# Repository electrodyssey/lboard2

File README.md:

experimental sound processing board with XC6SLX9-TQG144 and TLV320AIC3204

Work is in progress. 

Currently board is capable of receiving and sending the audio samples with a codec and passes the loopback test from FPGA pins.

FPGA bitstream config is stored inside the STM32F401RE internal flash.

Quick and dirty firmware loader is here: https://github.com/electrodyssey/lboard2flashboot

Working full-duplex aic3204 configuration script is saved in aic3204script directory:

codec receives: MCLK = 11.2896 MHz,

and generates: BLCK = 2.8224 MHz,

WCLK = 44.1 kHz

Please check the CHANGELOG  for the updates

Block diagram:

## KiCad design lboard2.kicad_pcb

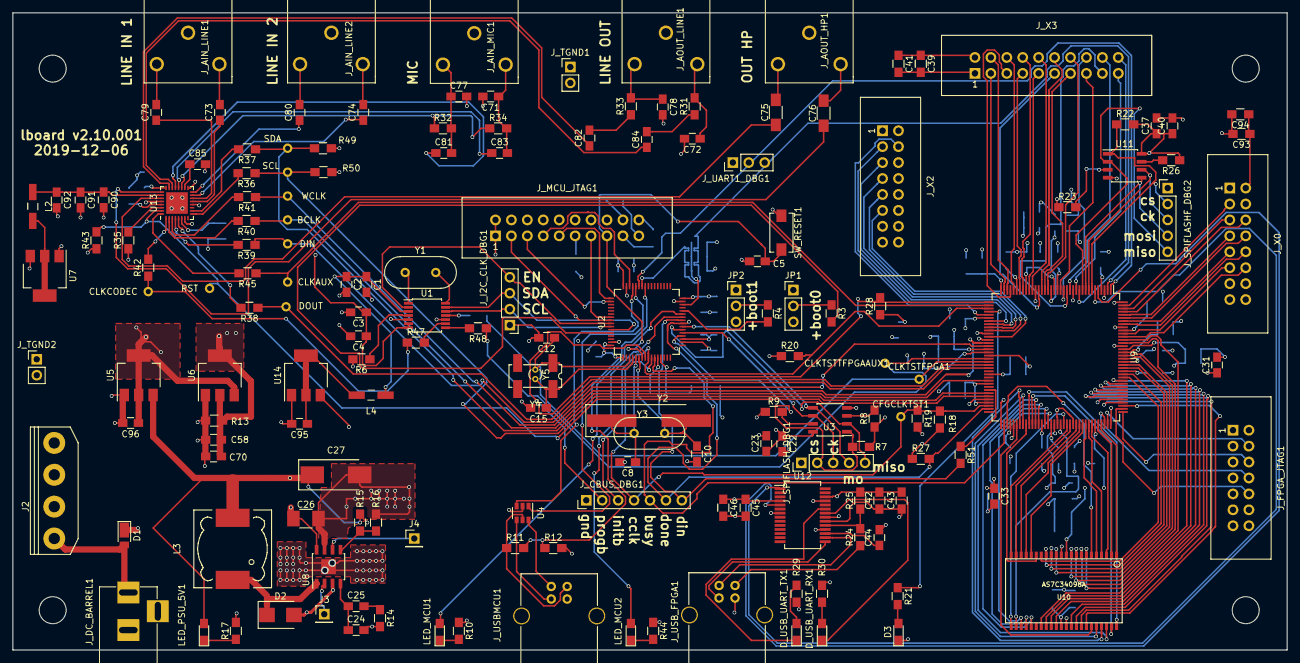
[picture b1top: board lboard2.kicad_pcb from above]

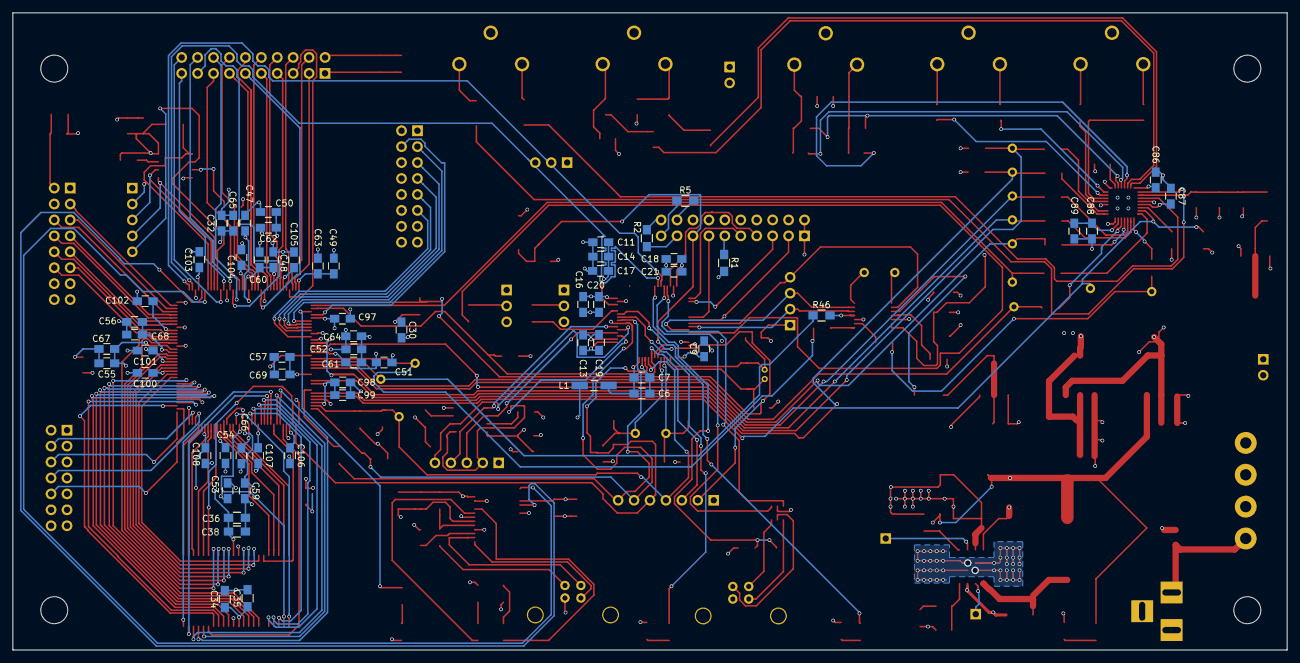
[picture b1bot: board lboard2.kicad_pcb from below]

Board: 4 copper layers, 203.2 x 101.6 mm, 230 parts (61 on the bottom side), 211 nets.

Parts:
BCLK: TEST_1P; Measurement_Point_Round-TH_Small
C1, C3, C6, C13, C16, C18, C22, C37, C47, C48, C49, C50, C51, C52, C53, C54, C55, C56, C57, C58, C82, C84, C91: 1uF; C_0805_HandSoldering
C2, C4, C5, C7, C9, C17, C19, C20, C21, C23, C40, C44, C59, C60, C61, C62, C63, C64, C65, C66, C67, C68, C69, C70, C81, C83, C89, C90, C97, C98, C99, C100, C101, C102, C103, C104, C105, C106, C107, C108: 0.1; C_0805_HandSoldering
C8, C10: 20pF; C_0805_HandSoldering
C11, C14: 2.2uF; C_0805_HandSoldering
C12, C15: 4.3pF; C_0805_HandSoldering
C24: 220pF; C_0805_HandSoldering
C25: 22nF; C_0805_HandSoldering
C26: 10uF x 25v; C_1210_HandSoldering
C27: 330uF; CP_Tantalum_Case-D_EIA-7343-31_Hand
C30, C31, C32, C33, C85, C86, C87, C88, C92, C95, C96: 10uF; C_0805_HandSoldering
C34, C36, C39, C42, C45, C93: 1uF; R_0805_HandSoldering
C35, C38, C41, C43, C46, C94: 0.1; R_0805_HandSoldering
C71, C77: DNP; C_0805_HandSoldering
C72, C78: 47nF; C_0805_HandSoldering
C73, C74, C79, C80: 0.47uF; C_0805_HandSoldering
C75, C76: 47uF; C_1206_HandSoldering
CFGCLKTST1: TEST_1P; Measurement_Point_Round-TH_Small
CLKAUX: TEST_1P; Measurement_Point_Round-TH_Small
CLKCODEC: TEST_1P; Measurement_Point_Round-TH_Small
CLKTSTFPGA1: TEST_1P; Measurement_Point_Round-TH_Small
CLKTSTTFPGAAUX1: TEST_1P; Measurement_Point_Round-TH_Small
D1: DFLS1100-7; D_PowerDI-123
D2: D_Schottky; D_SMB
D3: LED; LED_0805_HandSoldering
DIN: TEST_1P; Measurement_Point_Round-TH_Small
DOUT: TEST_1P; Measurement_Point_Round-TH_Small
D_USB_UART_RX1: LED; LED_0805_HandSoldering
D_USB_UART_TX1: LED; LED_0805_HandSoldering
J2: Conn_01x04; ATX-PSU-MOLEX-4PIN-5.08mm
J3: PSU_SYNC; Pin_Header_Straight_1x01_Pitch2.54mm
J4: PSU_REF; Pin_Header_Straight_1x01_Pitch2.54mm
JP1, JP2: Jumper_NC_Dual; Pin_Header_Straight_1x03_Pitch2.54mm
J_AIN_LINE1, J_AIN_LINE2: Audio-Jack-3; audiosock-3.5-3pin
J_AIN_MIC1: Audio-Jack-3; audiosock-3.5-3pin
J_AOUT_HP1: Audio-Jack-3; audiosock-3.5-3pin
J_AOUT_LINE1: Audio-Jack-3; audiosock-3.5-3pin
J_CBUS_DBG1: Conn_01x07_Male; Pin_Header_Straight_1x07_Pitch2.54mm
J_DC_BARREL1: Barrel_Jack; BARREL_JACK
J_FPGA_JTAG1: Conn_02x07_Odd_Even; IDC_Header_Straight_14pins
J_I2C_CLK_DBG1: Conn_01x04; Pin_Header_Straight_1x04_Pitch2.54mm
J_MCU_JTAG1: Conn_02x10_Odd_Even; IDC_Header_Straight_20pins
J_SPIFLASHF_DBG2: Conn_01x05; Pin_Header_Straight_1x05_Pitch2.54mm
J_SPIFLASH_DBG1: Conn_01x05; Pin_Header_Straight_1x05_Pitch2.54mm
J_TGND1, J_TGND2: TEST_2P; Pin_Header_Straight_1x02_Pitch2.54mm
J_UART1_DBG1: Conn_01x03; Pin_Header_Straight_1x03_Pitch2.54mm
J_USBMCU1: USB_B
J_USB_FPGA1: USB_B
J_X0, J_X2: Conn_02x08_Odd_Even; IDC_Header_Straight_16pins
J_X3: Conn_02x10_Odd_Even; IDC_Header_Straight_20pins
L1, L2, L4: Ferrite_Bead; Choke_SMD_1206_Handsoldering
L3: 15uH; Choke_SMD_12x12mm_h8mm
LED_MCU1, LED_MCU2: LED; LED_0805_HandSoldering
LED_PSU_5V1: LED; LED_0805_HandSoldering
MH0, MH1, MH2, MH3: MountingHole_4.3mm_M4_DIN965
R1, R2, R3, R4, R5, R8, R9, R22, R23, R25, R26, R49, R50: 10k; R_0805_HandSoldering
R6: 10k DNP; R_0805_HandSoldering
R7: DNP; R_0805_HandSoldering
R10, R44: 120; R_0805_HandSoldering
R11: 47k; R_0805_HandSoldering
R12: 68k; R_0805_HandSoldering
R13: 390; R_0805_HandSoldering
R14, R35, R43: 4.7k; R_0805_HandSoldering
R15: 12k; R_0805_HandSoldering
R16: 3.9k; R_0805_HandSoldering
R17: 220; R_0805_HandSoldering
R18, R19, R31, R33: 100; R_0805_HandSoldering
R20, R24, R28: 4k7; R_0805_HandSoldering
R21, R27, R29, R30: 330; R_0805_HandSoldering
R32, R34: 2.7k; R_0805_HandSoldering
R36, R37, R38, R39, R40, R41: 27; R_0805_HandSoldering
R42, R45, R51: 10; R_0805_HandSoldering
R46, R47, R48: 18; R_0805_HandSoldering
RST: TEST_1P; Measurement_Point_Round-TH_Small
SCL: TEST_1P; Measurement_Point_Round-TH_Small
SDA: TEST_1P; Measurement_Point_Round-TH_Small
SW_RESET1: SW_Push; SW_SPST_EVQPE1
U1: CDCE913PW; TSSOP-14_4.4x5mm_Pitch0.65mm
U2: STM32F401RBTx; LQFP-64_10x10mm_Pitch0.5mm
U3, U11: M25P16-VME; SOIC-8_3.9x4.9mm_Pitch1.27mm
U4: USBLC6-2SC6; SOT-23-6
U5: NCP1117-3.3_SOT223; SOT-223-3_TabPin2
U6: AMS1117-ADJ; SOT-223-3_TabPin2
U7: AMS1117-33; SOT-223-3_TabPin2
U8: L5973D; SOIC-8-1EP_3.9x4.9mm_Pitch1.27mm
U9: XC6SLX9-TQG144; LQFP-144_20x20mm_Pitch0.5mm
U10: AS7C34098A; tsop2-44
U12: FT232RL; SSOP-28_5.3x10.2mm_Pitch0.65mm
U13: TLV320AIC3204; QFN-32-1EP_5x5mm_Pitch0.5mm
U14: AMS1117-1.8; SOT-223-3_TabPin2
WCLK: TEST_1P; Measurement_Point_Round-TH_Small
Y1: 27MHz; Crystal_HC49-4H_Vertical
Y2: 8MHz; Crystal_SMD_HC49-SD_HandSoldering
Y3: DNP; Crystal_HC49-U_Vertical
Y4: ABS25-32.768KHZ-6-T; Crystal_SMD_SeikoEpson_MC306-4pin_8.0x3.2mm_HandSoldering
Y5: DNP32; Crystal_DS10_d1.0mm_l4.3mm_Vertical

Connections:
+1V2: C48.1, C50.1, C52.1, C54.1, C56.1, C58.1, C60.1, C62.1, C64.1, C66.1, C68.1, C70.1, R13.1, U6.2, U9.19, U9.28, U9.52, U9.89, U9.128
+1V8: C1.1, C2.1, L4.1, U1.3
+3.3VA: C90.1, C91.1, C92.1, L2.1, U13.26
+3V3: C3.1, C4.1, C9.1, C13.1, C16.1, C18.1, C19.1, C20.1, C21.1, C22.1, C23.1, C30.1, C31.1, C32.1, C33.1, C34.1, C35.1, C36.1, C37.1, C38.1, C39.1, C40.1, C41.1, C45.1, C46.1, C47.1, C49.1, C51.1, C53.1, C55.1, C57.1, C59.1, C61.1, C63.1, C65.1, C67.1, C69.1, C88.1, C89.1, C93.1, C94.1, C96.1, C97.1, C98.1, C99.1, C100.1, C101.1, C102.1, C103.1, C104.1, C105.1, C106.1, C107.1, C108.1, JP1.3, JP2.3, J_FPGA_JTAG1.2, J_MCU_JTAG1.1, J_MCU_JTAG1.2, J_X0.2, J_X2.2, J_X3.2, L1.2, R6.2, R7.1, R8.1, R9.1, R18.1, R20.1, R22.2, R23.1, R26.1, R27.1, R28.1, R29.1, R30.1, R35.1, R49.1, R50.1, U1.6, U1.7, U2.1, U2.19, U2.32, U2.48, U2.64, U3.8, U5.2, U6.3, U9.4, U9.18, U9.20, U9.31, U9.36, U9.42, U9.53, U9.60, U9.63, U9.69, U9.76, U9.86, U9.90, U9.103, U9.122, U9.125, U9.129, U9.135, U10.11, U10.33, U11.8, U12.4, U13.6, U14.3
+5V: C27.1, C42.1, C43.1, L3.2, LED_PSU_5V1.2, R15.1, U5.3, U7.3, U12.20
+12V: D1.2, J2.1, J_DC_BARREL1.1
/CODEC/CLK_CODEC: CLKCODEC.1, R42.1, R47.1
/CODEC/CODEC_BCLK: BCLK.1, R40.1, U9.50
/CODEC/CODEC_CLKAUX: CLKAUX.1, R45.1, U9.38
/CODEC/CODEC_DIN: DIN.1, R39.1, U9.58
/CODEC/CODEC_DOUT: DOUT.1, R38.1, U9.57
/CODEC/CODEC_RST: R43.2, RST.1, U9.67, U13.31
/CODEC/CODEC_SCL: R36.1, R50.2, SCL.1, U9.66
/CODEC/CODEC_SDA: R37.1, R49.2, SDA.1, U9.62
/CODEC/CODEC_WCLK: R41.1, U9.51, WCLK.1
/CODEC/HPL: C76.1, U13.25
/CODEC/HPR: C75.1, U13.27
/CODEC/IN1_L: C73.1, U13.13
/CODEC/IN1_R: C79.1, U13.14
/CODEC/IN2_L: C74.1, U13.15
/CODEC/IN2_R: C80.1, U13.16
/CODEC/IN3_L: C83.1, U13.20
/CODEC/IN3_R: C81.1, U13.21
/CODEC/LOL: C84.1, U13.22
/CODEC/LOR: C82.1, U13.23
/CODEC/MICBIAS: R32.1, R34.1, U13.19
/FPGA/CBUS_BUSY: J_CBUS_DBG1.5, U2.11, U9.74
/FPGA/CBUS_CLOCK: CFGCLKTST1.1, J_CBUS_DBG1.4, R18.2, R19.1, U2.10, U9.70
/FPGA/CBUS_DATA: J_CBUS_DBG1.7, R51.2, U2.25
/FPGA/CBUS_DONE: J_CBUS_DBG1.6, R27.2, U2.24, U9.71
/FPGA/CBUS_INITB: J_CBUS_DBG1.3, R20.2, U2.9, U9.39
/FPGA/CBUS_PROGB: J_CBUS_DBG1.2, R28.2, U2.8, U9.37
/FPGA/CLK_FPGA: CLKTSTFPGA1.1, R46.1, U9.56
/FPGA/CLK_FPGA_AUX: CLKTSTTFPGAAUX1.1, R48.1, U9.55
/FPGA/RAM_A0: U9.105, U10.1
/FPGA/RAM_A1: U9.104, U10.2
/FPGA/RAM_A2: U9.102, U10.3
/FPGA/RAM_A3: U9.101, U10.4
/FPGA/RAM_A4: U9.100, U10.5
/FPGA/RAM_A5: U9.99, U10.18
/FPGA/RAM_A6: U9.98, U10.19
/FPGA/RAM_A7: U9.97, U10.20
/FPGA/RAM_A8: U9.95, U10.21
/FPGA/RAM_A9: U9.94, U10.22
/FPGA/RAM_A10: U9.93, U10.23
/FPGA/RAM_A11: U9.92, U10.24
/FPGA/RAM_A12: U9.88, U10.25
/FPGA/RAM_A13: U9.87, U10.26
/FPGA/RAM_A14: U9.85, U10.27
/FPGA/RAM_A15: U9.84, U10.42
/FPGA/RAM_A16: U9.83, U10.43
/FPGA/RAM_A17: U9.82, U10.44
/FPGA/RAM_CE: U9.75, U10.6
/FPGA/RAM_D1: U9.132, U10.7
/FPGA/RAM_D2: U9.131, U10.8
/FPGA/RAM_D3: U9.127, U10.9
/FPGA/RAM_D4: U9.126, U10.10
/FPGA/RAM_D5: U9.124, U10.13
/FPGA/RAM_D6: U9.123, U10.14
/FPGA/RAM_D7: U9.121, U10.15
/FPGA/RAM_D8: U9.120, U10.16
/FPGA/RAM_D9: U9.119, U10.29
/FPGA/RAM_D10: U9.118, U10.30
/FPGA/RAM_D11: U9.117, U10.31
/FPGA/RAM_D12: U9.116, U10.32
/FPGA/RAM_D13: U9.115, U10.35
/FPGA/RAM_D14: U9.114, U10.36
/FPGA/RAM_D15: U9.112, U10.37
/FPGA/RAM_D16: U9.111, U10.38
/FPGA/RAM_LB: U9.78, U10.39
/FPGA/RAM_OE: U9.79, U10.41
/FPGA/RAM_UB: U9.80, U10.40
/FPGA/RAM_WE: U9.81, U10.17
/FPGA/SPIFL_CLK: J_SPIFLASHF_DBG2.3, U9.8, U11.6
/FPGA/SPIFL_CS: J_SPIFLASHF_DBG2.2, R22.1, U9.7, U11.1
/FPGA/SPIFL_MISO: J_SPIFLASHF_DBG2.5, U9.10, U11.2
/FPGA/SPIFL_MOSI: J_SPIFLASHF_DBG2.4, U9.9, U11.5
/FPGA/TCK: J_FPGA_JTAG1.6, U9.109
/FPGA/TDI: J_FPGA_JTAG1.10, U9.110
/FPGA/TDO: J_FPGA_JTAG1.8, U9.106
/FPGA/TMS: J_FPGA_JTAG1.4, U9.107
/FPGA/UART1_RX: J_UART1_DBG1.2, U2.43, U9.1
/FPGA/UART1_TX: J_UART1_DBG1.3, U2.42, U9.2
/FPGA/USB_UART_RX: U9.6, U12.1
/FPGA/USB_UART_TX: U9.5, U12.5
/FPGA/X0_L1_N: J_X0.3, U9.143
/FPGA/X0_L2_N: J_X0.6, U9.141
/FPGA/X0_L2_P: J_X0.5, U9.142
/FPGA/X0_L3_N: J_X0.8, U9.139
/FPGA/X0_L3_P: J_X0.7, U9.140
/FPGA/X0_L4_N: J_X0.10, U9.137
/FPGA/X0_L4_P: J_X0.9, U9.138
/FPGA/X0_L34_N: J_X0.12, U9.133
/FPGA/X0_L34_P: J_X0.11, U9.134
/FPGA/X2_L48P: J_X2.11, U9.48
/FPGA/X2_L49N: J_X2.7, U9.45
/FPGA/X2_L49P: J_X2.9, U9.46
/FPGA/X2_L62N: J_X2.3, U9.43
/FPGA/X2_L62P: J_X2.5, U9.44
/FPGA/X2_L64P: J_X2.4, U9.41
/FPGA/X3_L1_N: J_X3.4, U9.34
/FPGA/X3_L1_P: J_X3.3, U9.35
/FPGA/X3_L2_N: J_X3.6, U9.32
/FPGA/X3_L2_P: J_X3.5, U9.33
/FPGA/X3_L36_N: J_X3.8, U9.29
/FPGA/X3_L36_P: J_X3.7, U9.30
/FPGA/X3_L37_N: J_X3.10, U9.26
/FPGA/X3_L37_P: J_X3.9, U9.27
/FPGA/X3_L41_N: J_X3.12, U9.23
/FPGA/X3_L41_P: J_X3.11, U9.24
/FPGA/X3_L42_N: J_X3.14, U9.21
/FPGA/X3_L42_P: J_X3.13, U9.22
/FPGA/X3_L43_N: J_X3.16, U9.16
/FPGA/X3_L43_P: J_X3.15, U9.17
/FPGA/X3_L44_N: J_X3.18, U9.14
/FPGA/X3_L44_P: J_X3.17, U9.15
/FPGA/X3_L49_N: J_X3.20, U9.11
/FPGA/X3_L49_P: J_X3.19, U9.12
/MCU/BOOT_0: R3.2, U2.60
/MCU/BOOT_1: R4.2, U2.28
/MCU/I2C_CLK_ENA: J_I2C_CLK_DBG1.4, U1.2, U2.57
/MCU/I2C_CLK_SCL: J_I2C_CLK_DBG1.2, U1.12, U2.58
/MCU/I2C_CLK_SDA: J_I2C_CLK_DBG1.3, U1.13, U2.59
/MCU/NRST: C5.1, J_MCU_JTAG1.15, SW_RESET1.2, U2.7
/MCU/SPIFL_MISO: J_SPIFLASH_DBG1.5, U2.22, U3.2
/MCU/SPIFL_MOSI: J_SPIFLASH_DBG1.4, U2.23, U3.5
/MCU/SPIFL_NSS: J_SPIFLASH_DBG1.2, R7.2, U2.20, U3.1
/MCU/SPIFL_SCK: J_SPIFLASH_DBG1.3, U2.21, U3.6
/MCU/TCK_SWCLK: J_MCU_JTAG1.9, U2.49
/MCU/TDI: J_MCU_JTAG1.5, U2.50
/MCU/TDO_SWO: J_MCU_JTAG1.13, U2.55
/MCU/TMS_SWDIO: J_MCU_JTAG1.7, U2.46
/MCU/TRST: J_MCU_JTAG1.3, U2.56
/MCU/USB_DM: U2.44, U4.1
/MCU/USB_DP: U2.45, U4.3
/MCU/USB_VBUS_DETECT: R11.2, R12.1, U2.41
GND: C1.2, C2.2, C3.2, C4.2, C5.2, C6.2, C7.2, C8.2, C9.2, C10.2, C11.2, C12.2, C13.2, C14.2, C15.2, C16.2, C17.2, C18.2, C19.2, C20.2, C21.2, C22.2, C23.2, C24.2, C26.2, C27.2, C30.2, C31.2, C32.2, C33.2, C34.2, C35.2, C36.2, C37.2, C38.2, C39.2, C40.2, C41.2, C42.2, C43.2, C44.2, C45.2, C46.2, C47.2, C48.2, C49.2, C50.2, C51.2, C52.2, C53.2, C54.2, C55.2, C56.2, C57.2, C58.2, C59.2, C60.2, C61.2, C62.2, C63.2, C64.2, C65.2, C66.2, C67.2, C68.2, C69.2, C70.2, C71.2, C72.2, C77.2, C78.2, C85.2, C86.1, C87.1, C88.2, C89.2, C90.2, C91.2, C92.2, C93.2, C94.2, C95.2, C96.2, C97.2, C98.2, C99.2, C100.2, C101.2, C102.2, C103.2, C104.2, C105.2, C106.2, C107.2, C108.2, D2.2, D3.1, J2.2, J2.3, JP1.1, JP2.1, J_AIN_LINE1.3, J_AIN_LINE2.3, J_AIN_MIC1.3, J_AOUT_HP1.3, J_AOUT_LINE1.3, J_CBUS_DBG1.1, J_DC_BARREL1.2, J_DC_BARREL1.3, J_FPGA_JTAG1.1, J_FPGA_JTAG1.3, J_FPGA_JTAG1.5, J_FPGA_JTAG1.7, J_FPGA_JTAG1.9, J_FPGA_JTAG1.11, J_FPGA_JTAG1.13, J_I2C_CLK_DBG1.1, J_MCU_JTAG1.4, J_MCU_JTAG1.6, J_MCU_JTAG1.8, J_MCU_JTAG1.10, J_MCU_JTAG1.12, J_MCU_JTAG1.14, J_MCU_JTAG1.16, J_MCU_JTAG1.18, J_MCU_JTAG1.20, J_SPIFLASHF_DBG2.1, J_SPIFLASH_DBG1.1, J_TGND1.1, J_TGND1.2, J_TGND2.1, J_TGND2.2, J_UART1_DBG1.1, J_USBMCU1.4, J_USB_FPGA1.4, J_X0.1, J_X0.13, J_X0.14, J_X0.15, J_X0.16, J_X2.1, J_X2.6, J_X2.8, J_X2.10, J_X2.12, J_X2.14, J_X2.16, J_X3.1, R1.2, R2.2, R5.2, R10.1, R12.2, R13.2, R14.2, R16.2, R17.2, R19.2, R25.2, R43.1, R44.1, SW_RESET1.1, U1.5, U1.10, U2.12, U2.18, U2.31, U2.47, U2.63, U3.4, U4.2, U5.1, U6.1, U7.1, U8.3, U8.7, U9.3, U9.13, U9.25, U9.47, U9.49, U9.54, U9.68, U9.73, U9.77, U9.91, U9.96, U9.108, U9.113, U9.130, U9.136, U9.144, U10.12, U10.34, U11.4, U12.7, U12.18, U12.21, U12.25, U12.26, U13.7, U13.12, U13.17, U13.28, U14.1
unnamed: C6.1, C7.1, L1.1, U2.13
unnamed: C8.1, U2.5, Y2.1, Y3.1
unnamed: C10.1, U2.6, Y2.2, Y3.2
unnamed: C11.1, C14.1, C17.1, U2.30
unnamed: C12.1, U2.3, Y4.1, Y5.1
unnamed: C15.1, U2.4, Y4.4, Y5.2
unnamed: C24.1, C25.1, U8.4
unnamed: C25.2, R14.1
unnamed: C26.1, D1.1, U8.8
unnamed: C44.1, U12.17
unnamed: C71.1, C83.2, J_AIN_MIC1.1, R34.2
unnamed: C72.1, J_AOUT_LINE1.1, R31.2
unnamed: C73.2, J_AIN_LINE1.1
unnamed: C74.2, J_AIN_LINE2.1
unnamed: C75.2, J_AOUT_HP1.2
unnamed: C76.2, J_AOUT_HP1.1
unnamed: C77.1, C81.2, J_AIN_MIC1.2, R32.2
unnamed: C78.1, J_AOUT_LINE1.2, R33.2
unnamed: C79.2, J_AIN_LINE1.2
unnamed: C80.2, J_AIN_LINE2.2
unnamed: C82.2, R33.1
unnamed: C84.2, R31.1
unnamed: C85.1, U13.18
unnamed: C86.2, U13.24
unnamed: C87.2, U13.29
unnamed: C95.1, L4.2, U14.2
unnamed: D2.1, L3.1, U8.1
unnamed: D3.2, R21.2
unnamed: D_USB_UART_RX1.1, U12.22
unnamed: D_USB_UART_RX1.2, R30.2
unnamed: D_USB_UART_TX1.1, U12.23
unnamed: D_USB_UART_TX1.2, R29.2
unnamed: J3.1, U8.2
unnamed: J4.1, U8.6
unnamed: JP1.2, R3.1
unnamed: JP2.2, R4.1
unnamed: J_MCU_JTAG1.11, R1.1
unnamed: J_MCU_JTAG1.17, R2.1
unnamed: J_MCU_JTAG1.19, R5.1
unnamed: J_USBMCU1.1, R11.1, U4.5
unnamed: J_USBMCU1.2, U4.6
unnamed: J_USBMCU1.3, U4.4
unnamed: J_USB_FPGA1.1, R24.1
unnamed: J_USB_FPGA1.2, U12.16
unnamed: J_USB_FPGA1.3, U12.15
unnamed: L2.2, U7.2
unnamed: LED_MCU1.1, R10.2
unnamed: LED_MCU1.2, U2.27
unnamed: LED_MCU2.1, R44.2
unnamed: LED_MCU2.2, U2.26
unnamed: LED_PSU_5V1.1, R17.1
unnamed: R6.1, U1.4
unnamed: R8.2, U3.3
unnamed: R9.2, U3.7
unnamed: R15.2, R16.1, U8.5
unnamed: R21.1, U9.40
unnamed: R23.2, U11.3
unnamed: R24.2, R25.1, U12.19
unnamed: R26.2, U11.7
unnamed: R35.2, U13.30
unnamed: R36.2, U13.9
unnamed: R37.2, U13.10
unnamed: R38.2, U13.5
unnamed: R39.2, U13.4
unnamed: R40.2, U13.2
unnamed: R41.2, U13.3
unnamed: R42.2, U13.1
unnamed: R45.2, U13.32
unnamed: R46.2, U1.11
unnamed: R47.2, U1.9
unnamed: R48.2, U1.8
unnamed: R51.1, U9.65
unnamed: U1.1, Y1.1
unnamed: U1.14, Y1.2

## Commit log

2018-08-27 initial import
2018-08-27 README
2018-08-27 README updated
2018-08-27 README update
2018-09-27 fixed 3v3 supply on CDCE913 output pin ver. bump
2018-09-27 schematics pdf and board updates
2018-09-30 v2.8.001
    SPI flash NSS pullup resistor R7 is marked as DNP.
    LGPL license 3.0 added.
2018-10-02 work in progress notice, first pcb edition photo
2019-03-22 CSI_B must be left unconnected! ver. bump
2019-03-22 silkscreen description on a configuration bus
2019-03-23 Schematics updates
    U1 CDCDE913 Vctrl pin resistor is marked as DNP. Schematics pdf, gerbers and the photo were updated.
2019-03-23 Gerbers updated
2019-04-04 lboard2 added pullup resistors on a codec i2c bus
2019-04-04 lboard2 plot and gerbers updated for 2.9.005
    board and drawings updated for a codec i2c pullup resistors
2019-04-06 lboard2 v2.9.006
    added debug headers for spi flash, addedd R51 - serial termination resistor for a CBUS_DATA line
2019-04-06 lboard2 schematics pdf and gerbers updated
2019-06-08 block diagram and aic3204 configuration script are added
2019-06-08 README formatting
2020-01-02 codec word select and bit clock lines are now routed to an fpga global clock pins
